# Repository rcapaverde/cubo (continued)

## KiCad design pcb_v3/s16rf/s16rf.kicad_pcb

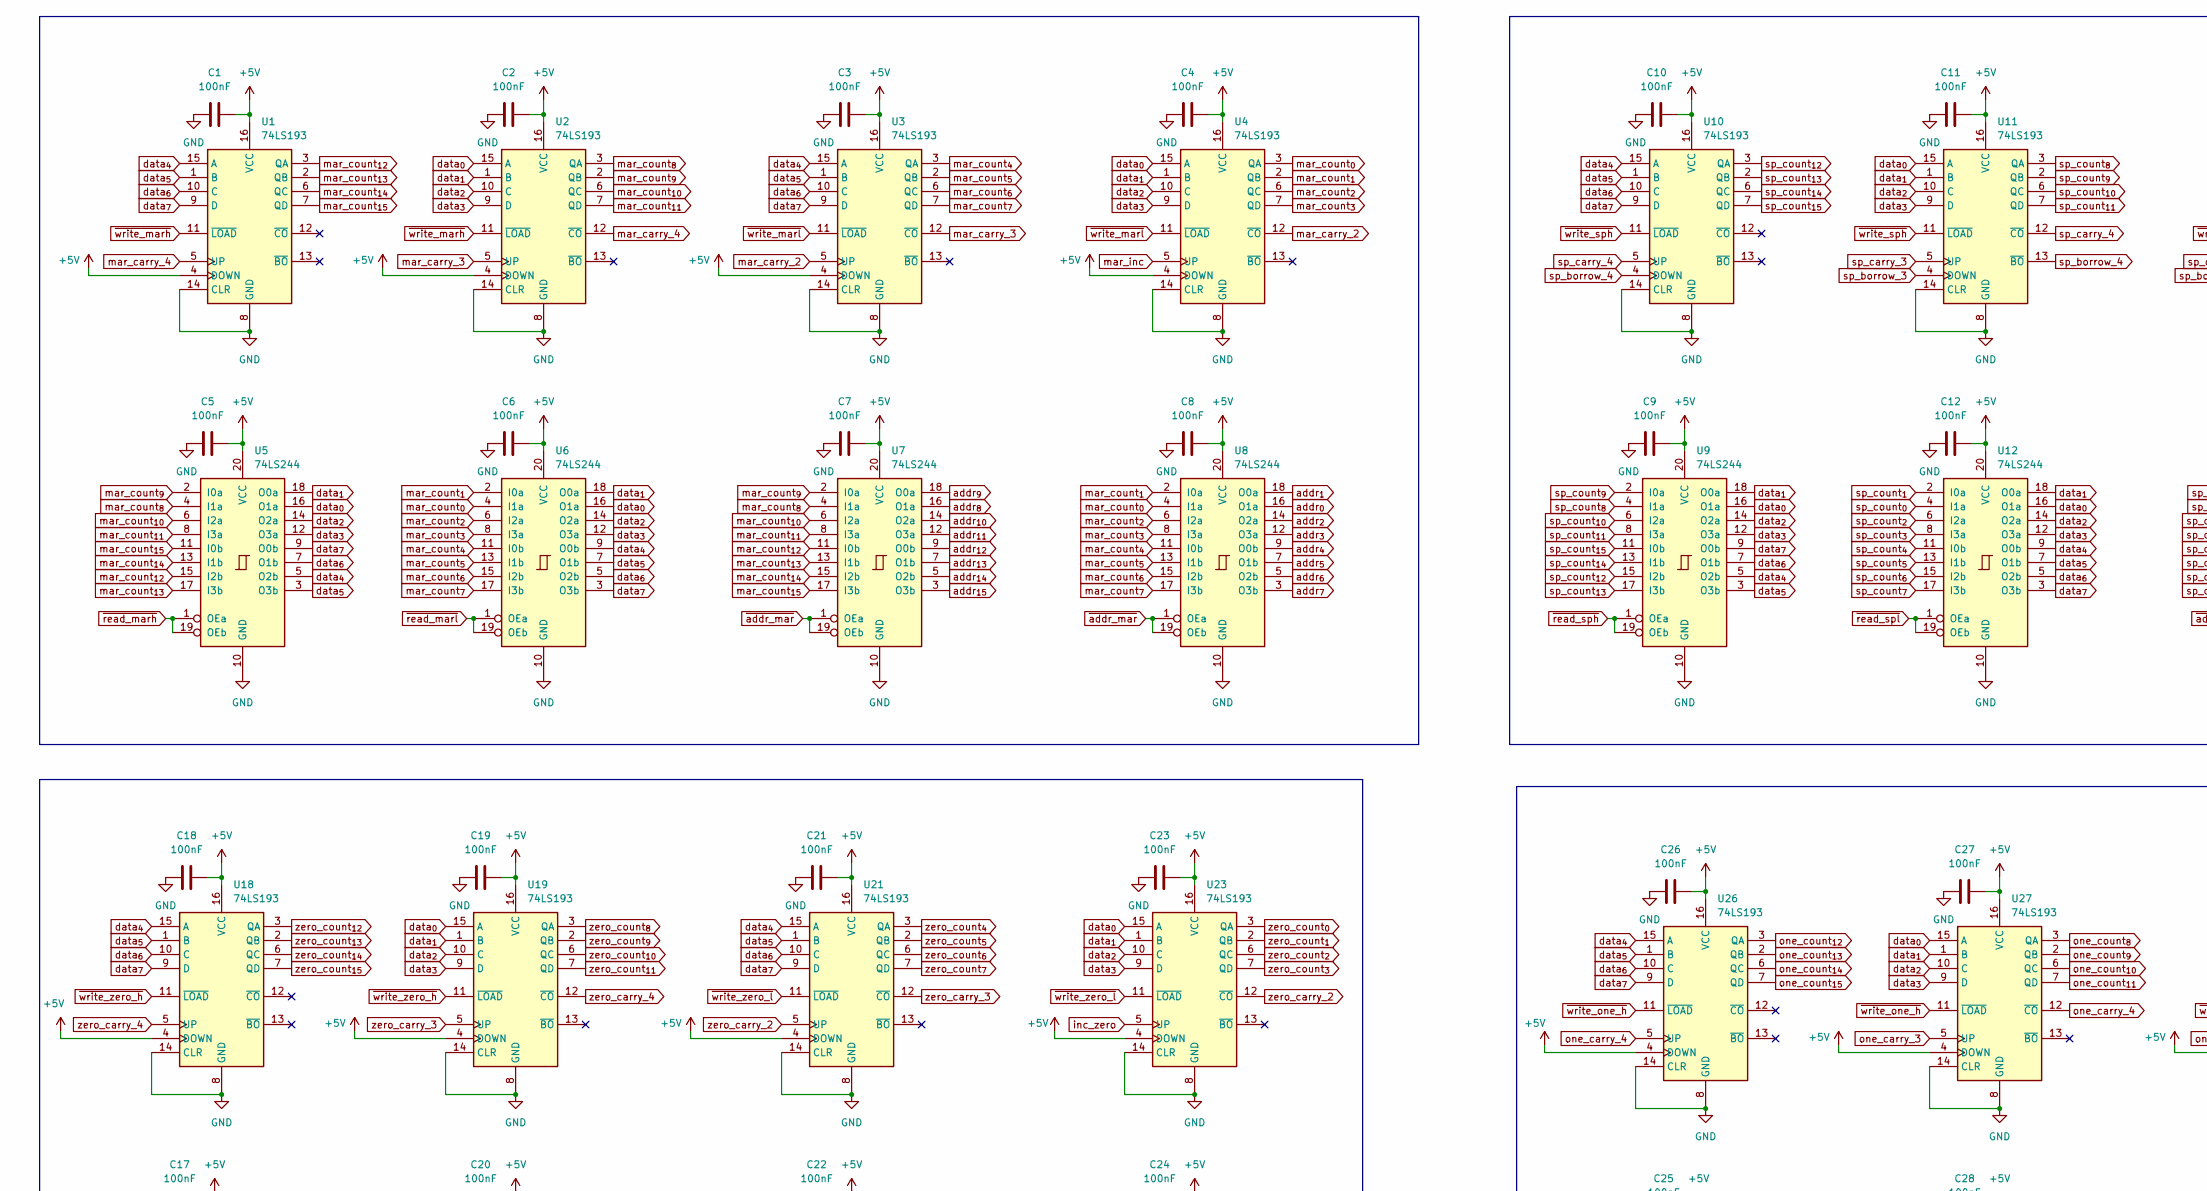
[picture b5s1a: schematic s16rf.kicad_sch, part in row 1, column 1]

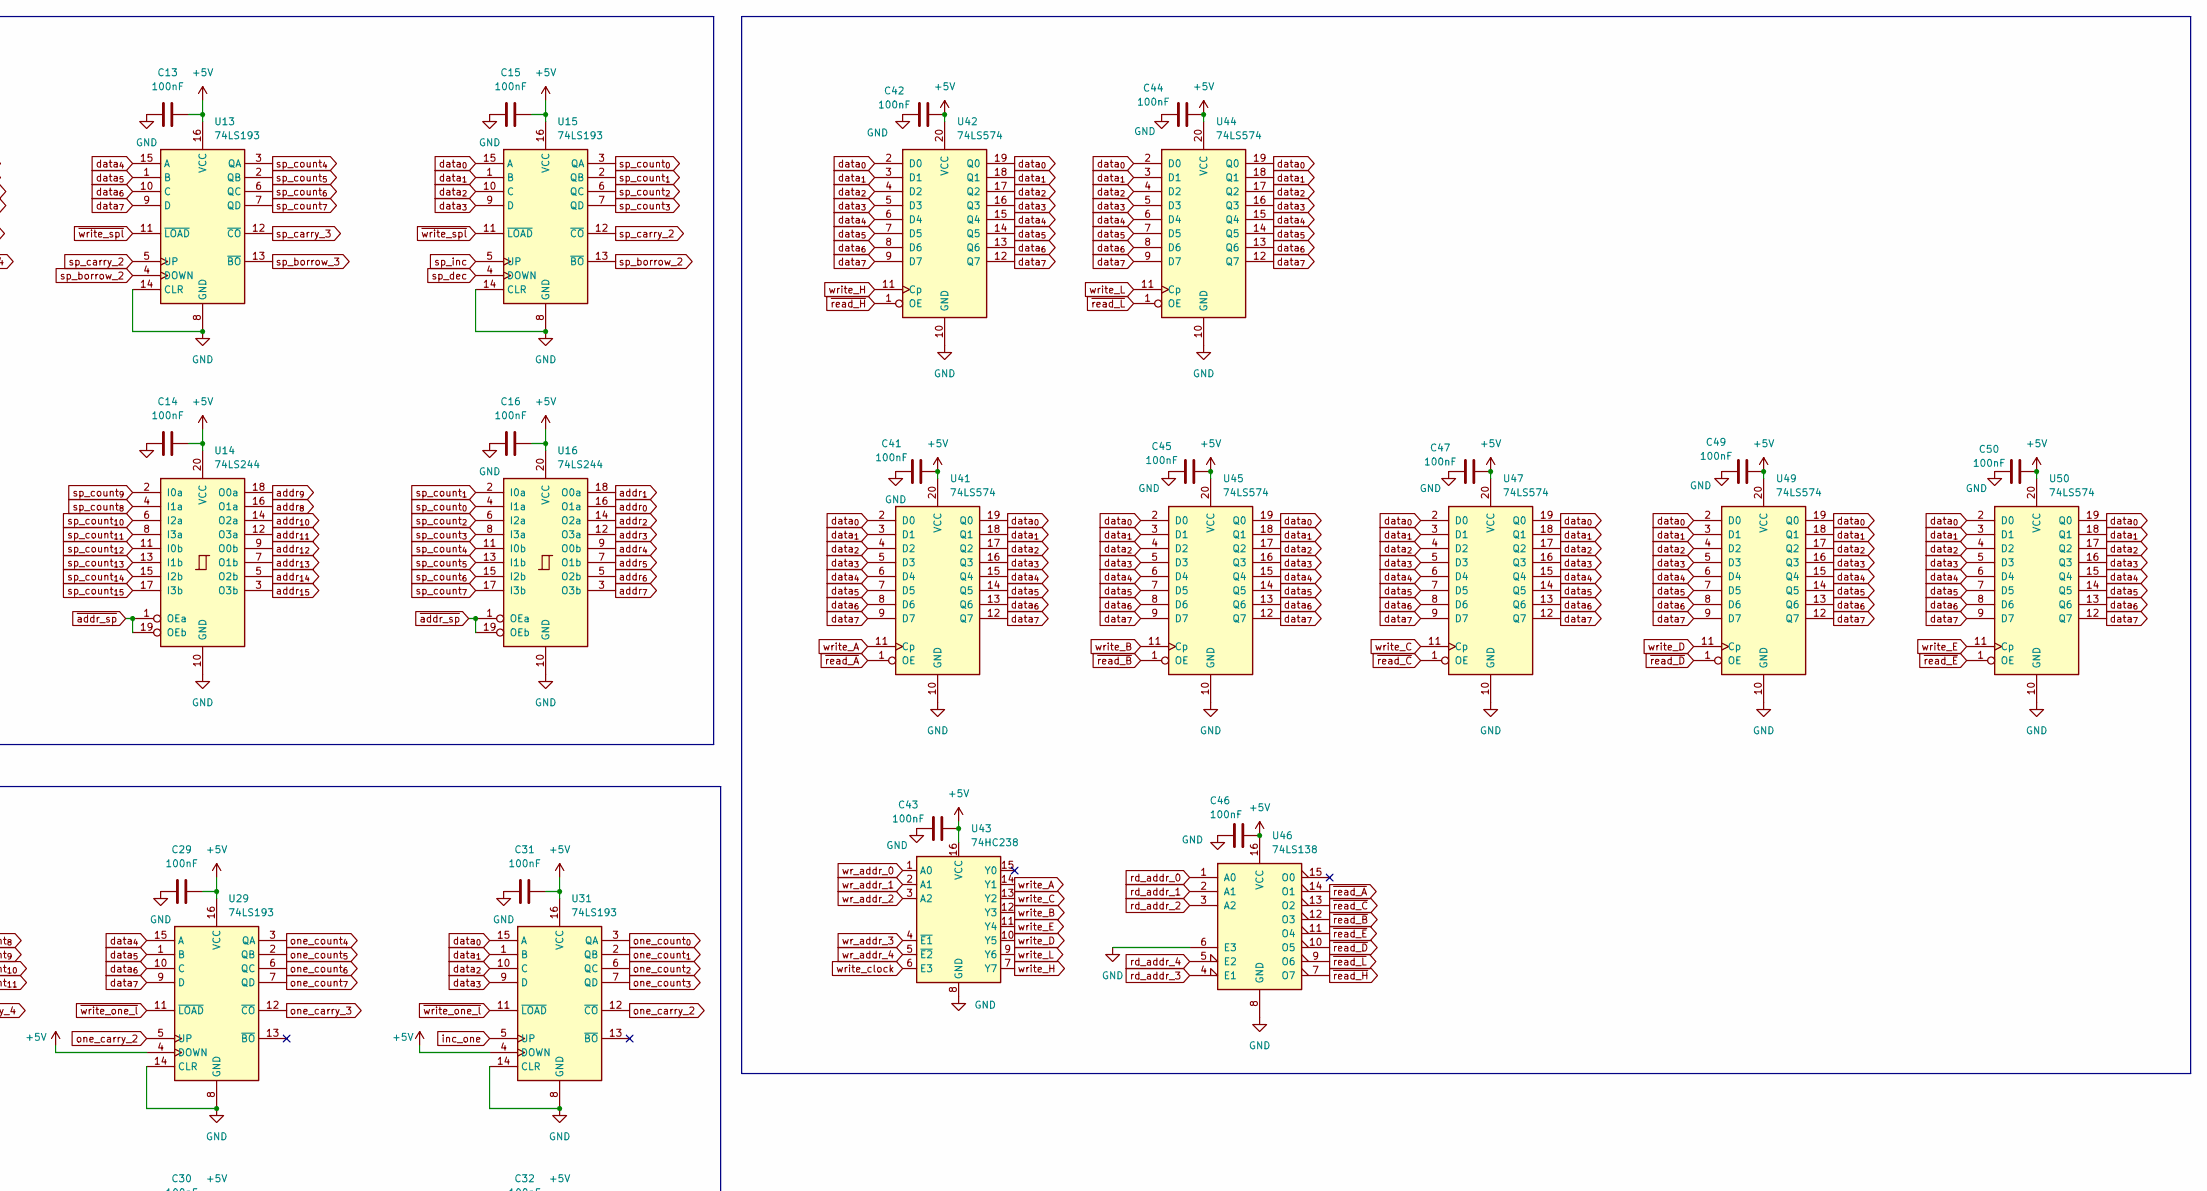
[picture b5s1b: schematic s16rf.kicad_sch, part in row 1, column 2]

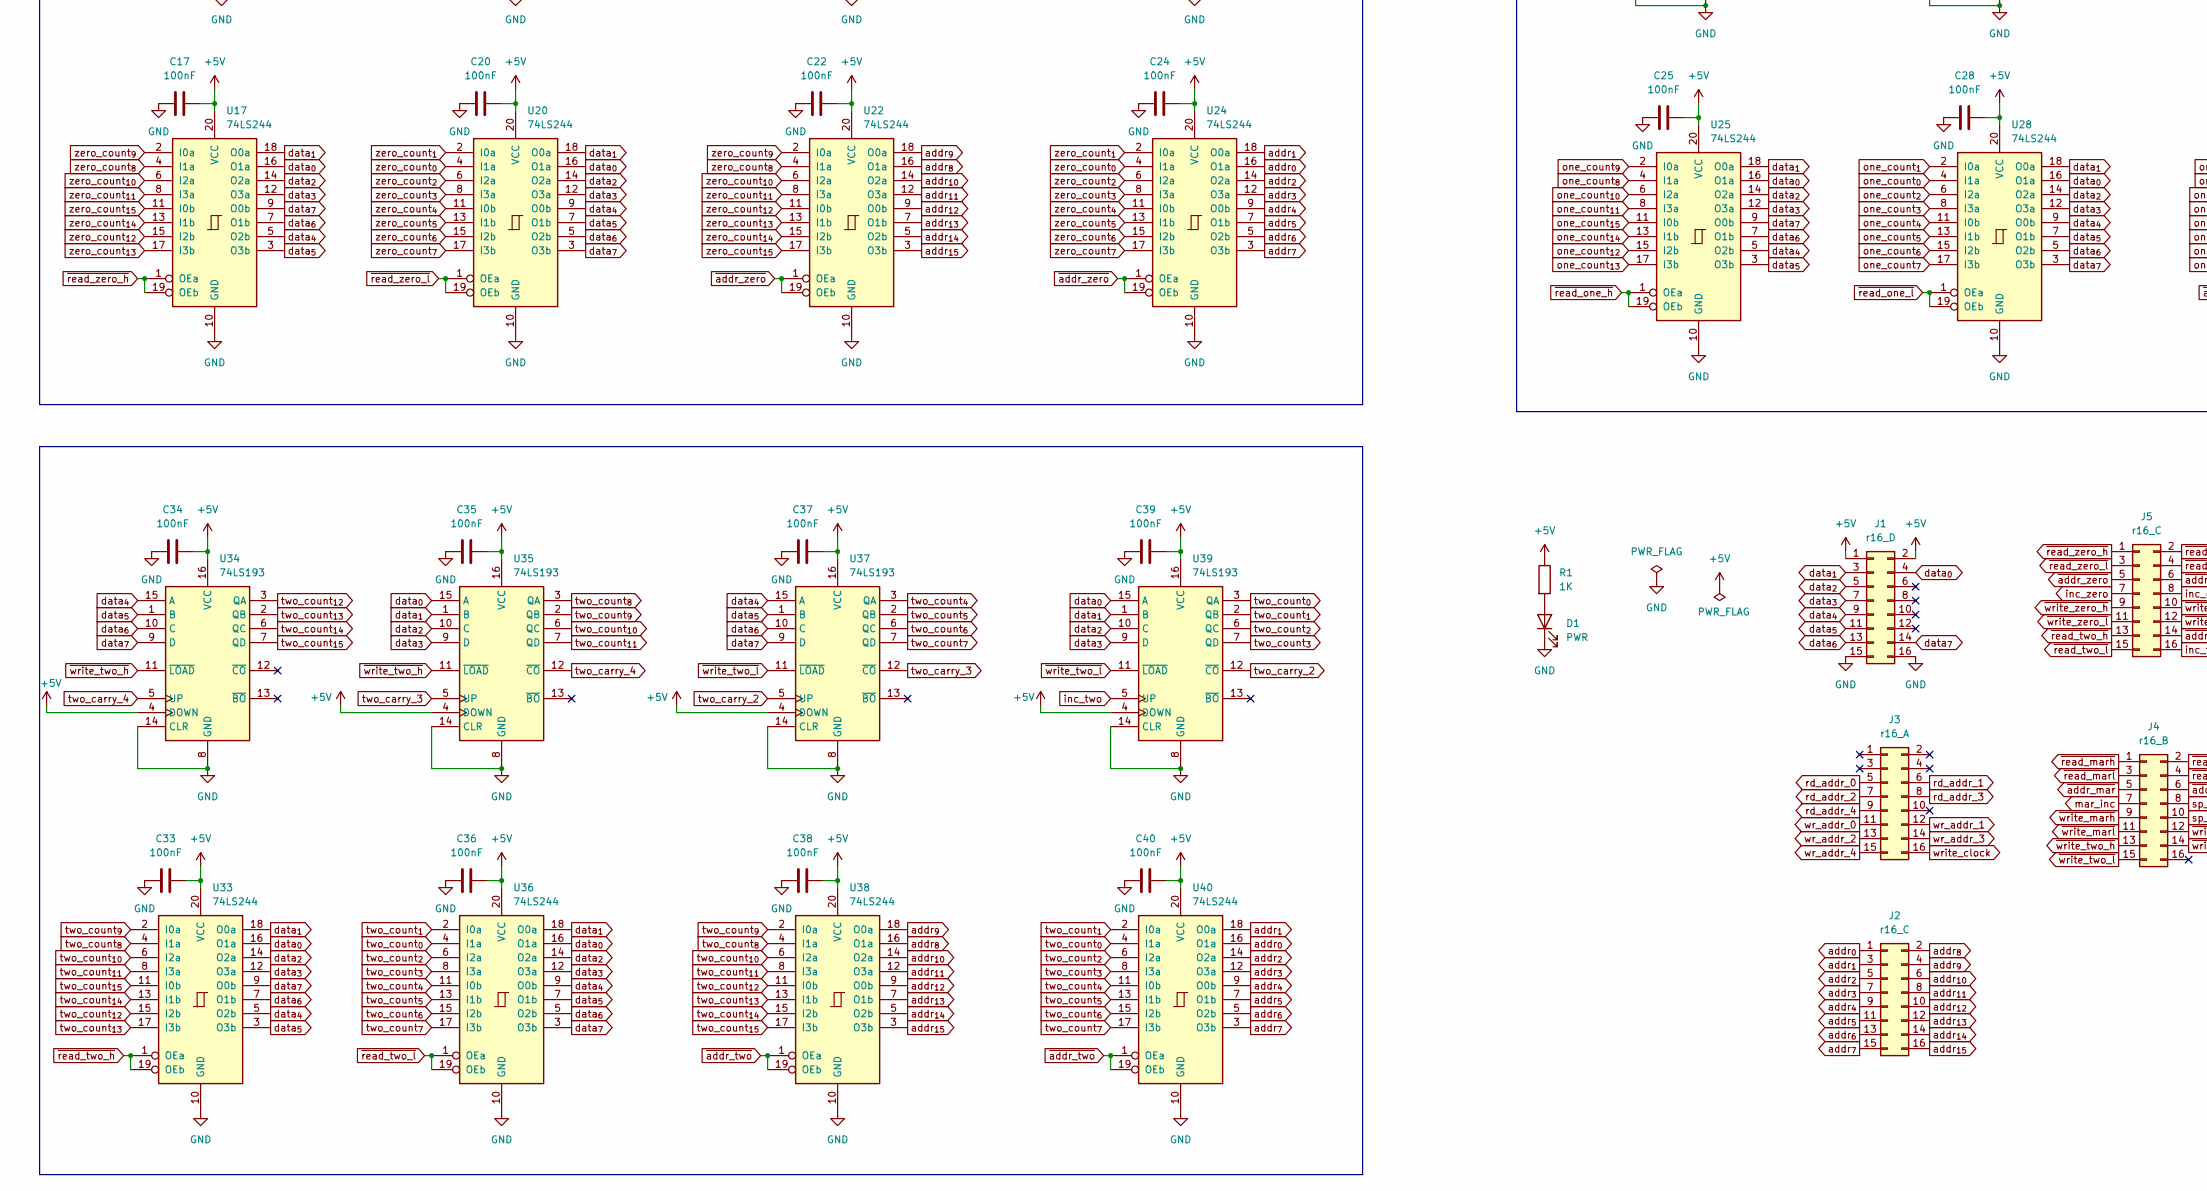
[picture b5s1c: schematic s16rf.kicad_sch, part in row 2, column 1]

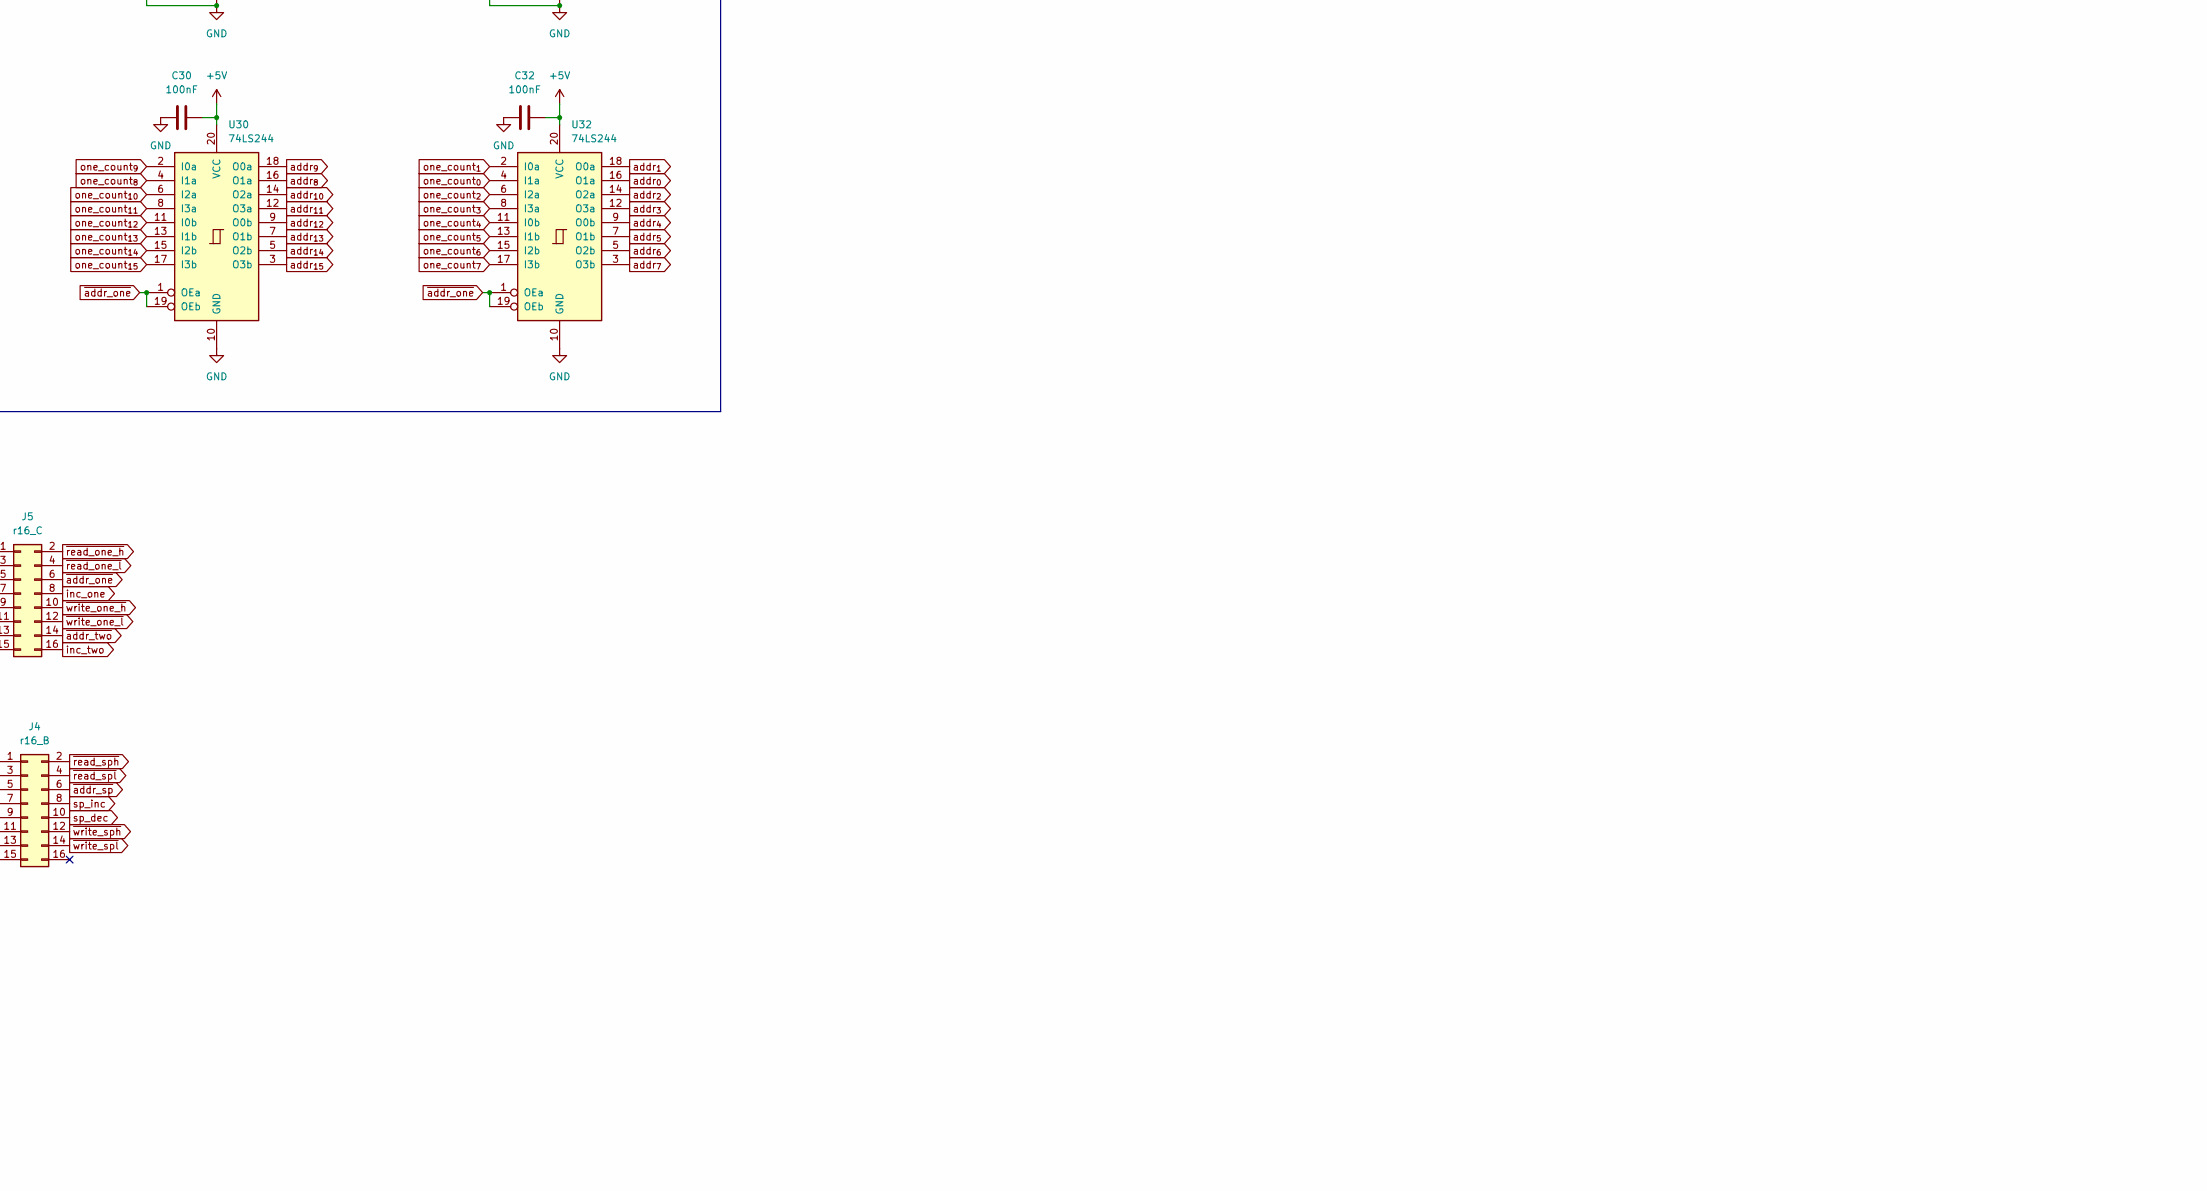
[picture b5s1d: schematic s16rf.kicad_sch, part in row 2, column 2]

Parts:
C1, C2, C3, C4, C5, C6, C7, C8, C9, C10, C11, C12, C13, C14, C15, C16, C17, C18, C19, C20, C21, C22, C23, C24, C25, C26, C27, C28, C29, C30, C31, C32, C33, C34, C35, C36, C37, C38, C39, C40, C41, C42, C43, C44, C45, C46, C47, C49, C50: 100nF; C_Disc_D5.1mm_W3.2mm_P5.00mm
D1: PWR; LED_D5.0mm
J1: r16_D; conector 02x08
J2, J5: r16_C; conector 02x08
J3: r16_A; conector 02x08
J4: r16_B; conector 02x08
R1: 1K; R_Axial_DIN0204_L3.6mm_D1.6mm_P7.62mm_Horizontal
U1, U2, U3, U4, U10, U11, U13, U15, U18, U19, U21, U23, U26, U27, U29, U31, U34, U35, U37, U39: 74LS193; DIP-16_W7.62mm
U5, U6, U7, U8, U9, U12, U14, U16, U17, U20, U22, U24, U25, U28, U30, U32, U33, U36, U38, U40: 74LS244; DIP-20_W7.62mm
U41, U42, U44, U45, U47, U49, U50: 74LS574; DIP-20_W7.62mm
U43: 74HC238; DIP-16_W7.62mm
U46: 74LS138; DIP-16_W7.62mm

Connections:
+5V: C1.2, C2.2, C3.2, C4.2, C5.2, C6.2, C7.2, C8.2, C9.2, C10.2, C11.2, C12.2, C13.2, C14.2, C15.2, C16.2, C17.2, C18.2, C19.2, C20.2, C21.2, C22.2, C23.2, C24.2, C25.2, C26.2, C27.2, C28.2, C29.2, C30.2, C31.2, C32.2, C33.2, C34.2, C35.2, C36.2, C37.2, C38.2, C39.2, C40.2, C41.2, C42.2, C43.2, C44.2, C45.2, C46.2, C47.2, C49.2, C50.2, J1.1, J1.2, R1.1, U1.4 (DOWN), U1.16 (VCC), U2.4 (DOWN), U2.16 (VCC), U3.4 (DOWN), U3.16 (VCC), U4.4 (DOWN), U4.16 (VCC), U5.20 (VCC), U6.20 (VCC), U7.20 (VCC), U8.20 (VCC), U9.20 (VCC), U10.16 (VCC), U11.16 (VCC), U12.20 (VCC), U13.16 (VCC), U14.20 (VCC), U15.16 (VCC), U16.20 (VCC), U17.20 (VCC), U18.4 (DOWN), U18.16 (VCC), U19.4 (DOWN), U19.16 (VCC), U20.20 (VCC), U21.4 (DOWN), U21.16 (VCC), U22.20 (VCC), U23.4 (DOWN), U23.16 (VCC), U24.20 (VCC), U25.20 (VCC), U26.4 (DOWN), U26.16 (VCC), U27.4 (DOWN), U27.16 (VCC), U28.20 (VCC), U29.4 (DOWN), U29.16 (VCC), U30.20 (VCC), U31.4 (DOWN), U31.16 (VCC), U32.20 (VCC), U33.20 (VCC), U34.4 (DOWN), U34.16 (VCC), U35.4 (DOWN), U35.16 (VCC), U36.20 (VCC), U37.4 (DOWN), U37.16 (VCC), U38.20 (VCC), U39.4 (DOWN), U39.16 (VCC), U40.20 (VCC), U41.20 (VCC), U42.20 (VCC), U43.16 (VCC), U44.20 (VCC), U45.20 (VCC), U46.16 (VCC), U47.20 (VCC), U49.20 (VCC), U50.20 (VCC)
GND: C1.1, C2.1, C3.1, C4.1, C5.1, C6.1, C7.1, C8.1, C9.1, C10.1, C11.1, C12.1, C13.1, C14.1, C15.1, C16.1, C17.1, C18.1, C19.1, C20.1, C21.1, C22.1, C23.1, C24.1, C25.1, C26.1, C27.1, C28.1, C29.1, C30.1, C31.1, C32.1, C33.1, C34.1, C35.1, C36.1, C37.1, C38.1, C39.1, C40.1, C41.1, C42.1, C43.1, C44.1, C45.1, C46.1, C47.1, C49.1, C50.1, D1.1 (K), J1.15, J1.16, U1.8 (GND), U1.14 (CLR), U2.8 (GND), U2.14 (CLR), U3.8 (GND), U3.14 (CLR), U4.8 (GND), U4.14 (CLR), U5.10 (GND), U6.10 (GND), U7.10 (GND), U8.10 (GND), U9.10 (GND), U10.8 (GND), U10.14 (CLR), U11.8 (GND), U11.14 (CLR), U12.10 (GND), U13.8 (GND), U13.14 (CLR), U14.10 (GND), U15.8 (GND), U15.14 (CLR), U16.10 (GND), U17.10 (GND), U18.8 (GND), U18.14 (CLR), U19.8 (GND), U19.14 (CLR), U20.10 (GND), U21.8 (GND), U21.14 (CLR), U22.10 (GND), U23.8 (GND), U23.14 (CLR), U24.10 (GND), U25.10 (GND), U26.8 (GND), U26.14 (CLR), U27.8 (GND), U27.14 (CLR), U28.10 (GND), U29.8 (GND), U29.14 (CLR), U30.10 (GND), U31.8 (GND), U31.14 (CLR), U32.10 (GND), U33.10 (GND), U34.8 (GND), U34.14 (CLR), U35.8 (GND), U35.14 (CLR), U36.10 (GND), U37.8 (GND), U37.14 (CLR), U38.10 (GND), U39.8 (GND), U39.14 (CLR), U40.10 (GND), U41.10 (GND), U42.10 (GND), U43.8 (GND), U44.10 (GND), U45.10 (GND), U46.6 (E3), U46.8 (GND), U47.10 (GND), U49.10 (GND), U50.10 (GND)
unnamed: D1.2 (A), R1.2
addr_{0}: J2.1, U8.16 (O1a), U16.16 (O1a), U24.16 (O1a), U32.16 (O1a), U40.16 (O1a)
addr_{1}: J2.3, U8.18 (O0a), U16.18 (O0a), U24.18 (O0a), U32.18 (O0a), U40.18 (O0a)
addr_{2}: J2.5, U8.14 (O2a), U16.14 (O2a), U24.14 (O2a), U32.14 (O2a), U40.14 (O2a)
addr_{3}: J2.7, U8.12 (O3a), U16.12 (O3a), U24.12 (O3a), U32.12 (O3a), U40.12 (O3a)
addr_{4}: J2.9, U8.9 (O0b), U16.9 (O0b), U24.9 (O0b), U32.9 (O0b), U40.9 (O0b)
addr_{5}: J2.11, U8.7 (O1b), U16.7 (O1b), U24.7 (O1b), U32.7 (O1b), U40.7 (O1b)
addr_{6}: J2.13, U8.5 (O2b), U16.5 (O2b), U24.5 (O2b), U32.5 (O2b), U40.5 (O2b)
addr_{7}: J2.15, U8.3 (O3b), U16.3 (O3b), U24.3 (O3b), U32.3 (O3b), U40.3 (O3b)
addr_{8}: J2.2, U7.16 (O1a), U14.16 (O1a), U22.16 (O1a), U30.16 (O1a), U38.16 (O1a)
addr_{9}: J2.4, U7.18 (O0a), U14.18 (O0a), U22.18 (O0a), U30.18 (O0a), U38.18 (O0a)
addr_{10}: J2.6, U7.14 (O2a), U14.14 (O2a), U22.14 (O2a), U30.14 (O2a), U38.14 (O2a)
addr_{11}: J2.8, U7.12 (O3a), U14.12 (O3a), U22.12 (O3a), U30.12 (O3a), U38.12 (O3a)
addr_{12}: J2.10, U7.9 (O0b), U14.9 (O0b), U22.9 (O0b), U30.9 (O0b), U38.9 (O0b)
addr_{13}: J2.12, U7.7 (O1b), U14.7 (O1b), U22.7 (O1b), U30.7 (O1b), U38.7 (O1b)
addr_{14}: J2.14, U7.5 (O2b), U14.5 (O2b), U22.5 (O2b), U30.5 (O2b), U38.5 (O2b)
addr_{15}: J2.16, U7.3 (O3b), U14.3 (O3b), U22.3 (O3b), U30.3 (O3b), U38.3 (O3b)
data_{0}: J1.4, U2.15 (A), U4.15 (A), U5.16 (O1a), U6.16 (O1a), U9.16 (O1a), U11.15 (A), U12.16 (O1a), U15.15 (A), U17.16 (O1a), U19.15 (A), U20.16 (O1a), U23.15 (A), U25.16 (O1a), U27.15 (A), U28.16 (O1a), U31.15 (A), U33.16 (O1a), U35.15 (A), U36.16 (O1a), U39.15 (A), U41.2 (D0), U41.19 (Q0), U42.2 (D0), U42.19 (Q0), U44.2 (D0), U44.19 (Q0), U45.2 (D0), U45.19 (Q0), U47.2 (D0), U47.19 (Q0), U49.2 (D0), U49.19 (Q0), U50.2 (D0), U50.19 (Q0)
data_{1}: J1.3, U2.1 (B), U4.1 (B), U5.18 (O0a), U6.18 (O0a), U9.18 (O0a), U11.1 (B), U12.18 (O0a), U15.1 (B), U17.18 (O0a), U19.1 (B), U20.18 (O0a), U23.1 (B), U25.18 (O0a), U27.1 (B), U28.18 (O0a), U31.1 (B), U33.18 (O0a), U35.1 (B), U36.18 (O0a), U39.1 (B), U41.3 (D1), U41.18 (Q1), U42.3 (D1), U42.18 (Q1), U44.3 (D1), U44.18 (Q1), U45.3 (D1), U45.18 (Q1), U47.3 (D1), U47.18 (Q1), U49.3 (D1), U49.18 (Q1), U50.3 (D1), U50.18 (Q1)
data_{2}: J1.5, U2.10 (C), U4.10 (C), U5.14 (O2a), U6.14 (O2a), U9.14 (O2a), U11.10 (C), U12.14 (O2a), U15.10 (C), U17.14 (O2a), U19.10 (C), U20.14 (O2a), U23.10 (C), U25.14 (O2a), U27.10 (C), U28.14 (O2a), U31.10 (C), U33.14 (O2a), U35.10 (C), U36.14 (O2a), U39.10 (C), U41.4 (D2), U41.17 (Q2), U42.4 (D2), U42.17 (Q2), U44.4 (D2), U44.17 (Q2), U45.4 (D2), U45.17 (Q2), U47.4 (D2), U47.17 (Q2), U49.4 (D2), U49.17 (Q2), U50.4 (D2), U50.17 (Q2)
data_{3}: J1.7, U2.9 (D), U4.9 (D), U5.12 (O3a), U6.12 (O3a), U9.12 (O3a), U11.9 (D), U12.12 (O3a), U15.9 (D), U17.12 (O3a), U19.9 (D), U20.12 (O3a), U23.9 (D), U25.12 (O3a), U27.9 (D), U28.12 (O3a), U31.9 (D), U33.12 (O3a), U35.9 (D), U36.12 (O3a), U39.9 (D), U41.5 (D3), U41.16 (Q3), U42.5 (D3), U42.16 (Q3), U44.5 (D3), U44.16 (Q3), U45.5 (D3), U45.16 (Q3), U47.5 (D3), U47.16 (Q3), U49.5 (D3), U49.16 (Q3), U50.5 (D3), U50.16 (Q3)
data_{4}: J1.9, U1.15 (A), U3.15 (A), U5.5 (O2b), U6.9 (O0b), U9.5 (O2b), U10.15 (A), U12.9 (O0b), U13.15 (A), U17.5 (O2b), U18.15 (A), U20.9 (O0b), U21.15 (A), U25.5 (O2b), U26.15 (A), U28.9 (O0b), U29.15 (A), U33.5 (O2b), U34.15 (A), U36.9 (O0b), U37.15 (A), U41.6 (D4), U41.15 (Q4), U42.6 (D4), U42.15 (Q4), U44.6 (D4), U44.15 (Q4), U45.6 (D4), U45.15 (Q4), U47.6 (D4), U47.15 (Q4), U49.6 (D4), U49.15 (Q4), U50.6 (D4), U50.15 (Q4)
data_{5}: J1.11, U1.1 (B), U3.1 (B), U5.3 (O3b), U6.7 (O1b), U9.3 (O3b), U10.1 (B), U12.7 (O1b), U13.1 (B), U17.3 (O3b), U18.1 (B), U20.7 (O1b), U21.1 (B), U25.3 (O3b), U26.1 (B), U28.7 (O1b), U29.1 (B), U33.3 (O3b), U34.1 (B), U36.7 (O1b), U37.1 (B), U41.7 (D5), U41.14 (Q5), U42.7 (D5), U42.14 (Q5), U44.7 (D5), U44.14 (Q5), U45.7 (D5), U45.14 (Q5), U47.7 (D5), U47.14 (Q5), U49.7 (D5), U49.14 (Q5), U50.7 (D5), U50.14 (Q5)
data_{6}: J1.13, U1.10 (C), U3.10 (C), U5.7 (O1b), U6.5 (O2b), U9.7 (O1b), U10.10 (C), U12.5 (O2b), U13.10 (C), U17.7 (O1b), U18.10 (C), U20.5 (O2b), U21.10 (C), U25.7 (O1b), U26.10 (C), U28.5 (O2b), U29.10 (C), U33.7 (O1b), U34.10 (C), U36.5 (O2b), U37.10 (C), U41.8 (D6), U41.13 (Q6), U42.8 (D6), U42.13 (Q6), U44.8 (D6), U44.13 (Q6), U45.8 (D6), U45.13 (Q6), U47.8 (D6), U47.13 (Q6), U49.8 (D6), U49.13 (Q6), U50.8 (D6), U50.13 (Q6)
data_{7}: J1.14, U1.9 (D), U3.9 (D), U5.9 (O0b), U6.3 (O3b), U9.9 (O0b), U10.9 (D), U12.3 (O3b), U13.9 (D), U17.9 (O0b), U18.9 (D), U20.3 (O3b), U21.9 (D), U25.9 (O0b), U26.9 (D), U28.3 (O3b), U29.9 (D), U33.9 (O0b), U34.9 (D), U36.3 (O3b), U37.9 (D), U41.9 (D7), U41.12 (Q7), U42.9 (D7), U42.12 (Q7), U44.9 (D7), U44.12 (Q7), U45.9 (D7), U45.12 (Q7), U47.9 (D7), U47.12 (Q7), U49.9 (D7), U49.12 (Q7), U50.9 (D7), U50.12 (Q7)
inc_one: J5.8, U31.5 (UP)
inc_two: J5.16, U39.5 (UP)
inc_zero: J5.7, U23.5 (UP)
mar_carry_2: U3.5 (UP), U4.12 (~CO)
mar_carry_3: U2.5 (UP), U3.12 (~CO)
mar_carry_4: U1.5 (UP), U2.12 (~CO)
mar_count_{0}: U4.3 (QA), U6.4 (I1a), U8.4 (I1a)
mar_count_{1}: U4.2 (QB), U6.2 (I0a), U8.2 (I0a)
mar_count_{2}: U4.6 (QC), U6.6 (I2a), U8.6 (I2a)
mar_count_{3}: U4.7 (QD), U6.8 (I3a), U8.8 (I3a)
mar_count_{4}: U3.3 (QA), U6.11 (I0b), U8.11 (I0b)
mar_count_{5}: U3.2 (QB), U6.13 (I1b), U8.13 (I1b)
mar_count_{6}: U3.6 (QC), U6.15 (I2b), U8.15 (I2b)
mar_count_{7}: U3.7 (QD), U6.17 (I3b), U8.17 (I3b)
mar_count_{8}: U2.3 (QA), U5.4 (I1a), U7.4 (I1a)
mar_count_{9}: U2.2 (QB), U5.2 (I0a), U7.2 (I0a)
mar_count_{10}: U2.6 (QC), U5.6 (I2a), U7.6 (I2a)
mar_count_{11}: U2.7 (QD), U5.8 (I3a), U7.8 (I3a)
mar_count_{12}: U1.3 (QA), U5.15 (I2b), U7.11 (I0b)
mar_count_{13}: U1.2 (QB), U5.17 (I3b), U7.13 (I1b)
mar_count_{14}: U1.6 (QC), U5.13 (I1b), U7.15 (I2b)
mar_count_{15}: U1.7 (QD), U5.11 (I0b), U7.17 (I3b)
mar_inc: J4.7, U4.5 (UP)
one_carry_2: U29.5 (UP), U31.12 (~CO)
one_carry_3: U27.5 (UP), U29.12 (~CO)
one_carry_4: U26.5 (UP), U27.12 (~CO)
one_count_{0}: U28.4 (I1a), U31.3 (QA), U32.4 (I1a)
one_count_{1}: U28.2 (I0a), U31.2 (QB), U32.2 (I0a)
one_count_{2}: U28.6 (I2a), U31.6 (QC), U32.6 (I2a)
one_count_{3}: U28.8 (I3a), U31.7 (QD), U32.8 (I3a)
one_count_{4}: U28.11 (I0b), U29.3 (QA), U32.11 (I0b)
one_count_{5}: U28.13 (I1b), U29.2 (QB), U32.13 (I1b)
one_count_{6}: U28.15 (I2b), U29.6 (QC), U32.15 (I2b)
one_count_{7}: U28.17 (I3b), U29.7 (QD), U32.17 (I3b)
one_count_{8}: U25.4 (I1a), U27.3 (QA), U30.4 (I1a)
one_count_{9}: U25.2 (I0a), U27.2 (QB), U30.2 (I0a)
one_count_{10}: U25.6 (I2a), U27.6 (QC), U30.6 (I2a)
one_count_{11}: U25.8 (I3a), U27.7 (QD), U30.8 (I3a)
one_count_{12}: U25.15 (I2b), U26.3 (QA), U30.11 (I0b)
one_count_{13}: U25.17 (I3b), U26.2 (QB), U30.13 (I1b)
one_count_{14}: U25.13 (I1b), U26.6 (QC), U30.15 (I2b)
one_count_{15}: U25.11 (I0b), U26.7 (QD), U30.17 (I3b)
rd_addr_0: J3.5, U46.1 (A0)
rd_addr_1: J3.6, U46.2 (A1)
rd_addr_2: J3.7, U46.3 (A2)
rd_addr_3: J3.8, U46.4 (E1)
rd_addr_4: J3.9, U46.5 (E2)
sp_borrow_2: U13.4 (DOWN), U15.13 (~BO)
sp_borrow_3: U11.4 (DOWN), U13.13 (~BO)
sp_borrow_4: U10.4 (DOWN), U11.13 (~BO)
sp_carry_2: U13.5 (UP), U15.12 (~CO)
sp_carry_3: U11.5 (UP), U13.12 (~CO)
sp_carry_4: U10.5 (UP), U11.12 (~CO)
sp_count_{0}: U12.4 (I1a), U15.3 (QA), U16.4 (I1a)
sp_count_{1}: U12.2 (I0a), U15.2 (QB), U16.2 (I0a)
sp_count_{2}: U12.6 (I2a), U15.6 (QC), U16.6 (I2a)
sp_count_{3}: U12.8 (I3a), U15.7 (QD), U16.8 (I3a)
sp_count_{4}: U12.11 (I0b), U13.3 (QA), U16.11 (I0b)
sp_count_{5}: U12.13 (I1b), U13.2 (QB), U16.13 (I1b)
sp_count_{6}: U12.15 (I2b), U13.6 (QC), U16.15 (I2b)
sp_count_{7}: U12.17 (I3b), U13.7 (QD), U16.17 (I3b)
sp_count_{8}: U9.4 (I1a), U11.3 (QA), U14.4 (I1a)
sp_count_{9}: U9.2 (I0a), U11.2 (QB), U14.2 (I0a)
sp_count_{10}: U9.6 (I2a), U11.6 (QC), U14.6 (I2a)
sp_count_{11}: U9.8 (I3a), U11.7 (QD), U14.8 (I3a)
sp_count_{12}: U9.15 (I2b), U10.3 (QA), U14.11 (I0b)
sp_count_{13}: U9.17 (I3b), U10.2 (QB), U14.13 (I1b)
sp_count_{14}: U9.13 (I1b), U10.6 (QC), U14.15 (I2b)
sp_count_{15}: U9.11 (I0b), U10.7 (QD), U14.17 (I3b)
sp_dec: J4.10, U15.4 (DOWN)
sp_inc: J4.8, U15.5 (UP)
two_carry_2: U37.5 (UP), U39.12 (~CO)
two_carry_3: U35.5 (UP), U37.12 (~CO)
two_carry_4: U34.5 (UP), U35.12 (~CO)
two_count_{0}: U36.4 (I1a), U39.3 (QA), U40.4 (I1a)
two_count_{1}: U36.2 (I0a), U39.2 (QB), U40.2 (I0a)
two_count_{2}: U36.6 (I2a), U39.6 (QC), U40.6 (I2a)
two_count_{3}: U36.8 (I3a), U39.7 (QD), U40.8 (I3a)
two_count_{4}: U36.11 (I0b), U37.3 (QA), U40.11 (I0b)
two_count_{5}: U36.13 (I1b), U37.2 (QB), U40.13 (I1b)
two_count_{6}: U36.15 (I2b), U37.6 (QC), U40.15 (I2b)
two_count_{7}: U36.17 (I3b), U37.7 (QD), U40.17 (I3b)
two_count_{8}: U33.4 (I1a), U35.3 (QA), U38.4 (I1a)
two_count_{9}: U33.2 (I0a), U35.2 (QB), U38.2 (I0a)
two_count_{10}: U33.6 (I2a), U35.6 (QC), U38.6 (I2a)
two_count_{11}: U33.8 (I3a), U35.7 (QD), U38.8 (I3a)
two_count_{12}: U33.15 (I2b), U34.3 (QA), U38.11 (I0b)
two_count_{13}: U33.17 (I3b), U34.2 (QB), U38.13 (I1b)
two_count_{14}: U33.13 (I1b), U34.6 (QC), U38.15 (I2b)
two_count_{15}: U33.11 (I0b), U34.7 (QD), U38.17 (I3b)
wr_addr_0: J3.11, U43.1 (A0)
wr_addr_1: J3.12, U43.2 (A1)
wr_addr_2: J3.13, U43.3 (A2)
wr_addr_3: J3.14, U43.4 (~E1)
wr_addr_4: J3.15, U43.5 (~E2)
write_A: U41.11 (Cp), U43.14 (Y1)
write_B: U43.12 (Y3), U45.11 (Cp)
write_C: U43.13 (Y2), U47.11 (Cp)
write_D: U43.10 (Y5), U49.11 (Cp)
write_E: U43.11 (Y4), U50.11 (Cp)
write_H: U42.11 (Cp), U43.7 (Y7)
write_L: U43.9 (Y6), U44.11 (Cp)
write_clock: J3.16, U43.6 (E3)
zero_carry_2: U21.5 (UP), U23.12 (~CO)
zero_carry_3: U19.5 (UP), U21.12 (~CO)
zero_carry_4: U18.5 (UP), U19.12 (~CO)
zero_count_{0}: U20.4 (I1a), U23.3 (QA), U24.4 (I1a)
zero_count_{1}: U20.2 (I0a), U23.2 (QB), U24.2 (I0a)
zero_count_{2}: U20.6 (I2a), U23.6 (QC), U24.6 (I2a)
zero_count_{3}: U20.8 (I3a), U23.7 (QD), U24.8 (I3a)
zero_count_{4}: U20.11 (I0b), U21.3 (QA), U24.11 (I0b)
zero_count_{5}: U20.13 (I1b), U21.2 (QB), U24.13 (I1b)
zero_count_{6}: U20.15 (I2b), U21.6 (QC), U24.15 (I2b)
zero_count_{7}: U20.17 (I3b), U21.7 (QD), U24.17 (I3b)
zero_count_{8}: U17.4 (I1a), U19.3 (QA), U22.4 (I1a)
zero_count_{9}: U17.2 (I0a), U19.2 (QB), U22.2 (I0a)
zero_count_{10}: U17.6 (I2a), U19.6 (QC), U22.6 (I2a)
zero_count_{11}: U17.8 (I3a), U19.7 (QD), U22.8 (I3a)
zero_count_{12}: U17.15 (I2b), U18.3 (QA), U22.11 (I0b)
zero_count_{13}: U17.17 (I3b), U18.2 (QB), U22.13 (I1b)
zero_count_{14}: U17.13 (I1b), U18.6 (QC), U22.15 (I2b)
zero_count_{15}: U17.11 (I0b), U18.7 (QD), U22.17 (I3b)
~addr_mar: J4.5, U7.1 (OEa), U7.19 (OEb), U8.1 (OEa), U8.19 (OEb)
~addr_one: J5.6, U30.1 (OEa), U30.19 (OEb), U32.1 (OEa), U32.19 (OEb)
~addr_sp: J4.6, U14.1 (OEa), U14.19 (OEb), U16.1 (OEa), U16.19 (OEb)
~addr_two: J5.14, U38.1 (OEa), U38.19 (OEb), U40.1 (OEa), U40.19 (OEb)
~addr_zero: J5.5, U22.1 (OEa), U22.19 (OEb), U24.1 (OEa), U24.19 (OEb)
~read_A: U41.1 (OE), U46.14 (O1)
~read_B: U45.1 (OE), U46.12 (O3)
~read_C: U46.13 (O2), U47.1 (OE)
~read_D: U46.10 (O5), U49.1 (OE)
~read_E: U46.11 (O4), U50.1 (OE)
~read_H: U42.1 (OE), U46.7 (O7)
~read_L: U44.1 (OE), U46.9 (O6)
~read_marh: J4.1, U5.1 (OEa), U5.19 (OEb)
~read_marl: J4.3, U6.1 (OEa), U6.19 (OEb)
~read_one_h: J5.2, U25.1 (OEa), U25.19 (OEb)
~read_one_l: J5.4, U28.1 (OEa), U28.19 (OEb)
~read_sph: J4.2, U9.1 (OEa), U9.19 (OEb)
~read_spl: J4.4, U12.1 (OEa), U12.19 (OEb)
~read_two_h: J5.13, U33.1 (OEa), U33.19 (OEb)
~read_two_l: J5.15, U36.1 (OEa), U36.19 (OEb)
~read_zero_h: J5.1, U17.1 (OEa), U17.19 (OEb)
~read_zero_l: J5.3, U20.1 (OEa), U20.19 (OEb)
~write_marh: J4.9, U1.11 (~LOAD), U2.11 (~LOAD)
~write_marl: J4.11, U3.11 (~LOAD), U4.11 (~LOAD)
~write_one_h: J5.10, U26.11 (~LOAD), U27.11 (~LOAD)
~write_one_l: J5.12, U29.11 (~LOAD), U31.11 (~LOAD)
~write_sph: J4.12, U10.11 (~LOAD), U11.11 (~LOAD)
~write_spl: J4.14, U13.11 (~LOAD), U15.11 (~LOAD)
~write_two_h: J4.13, U34.11 (~LOAD), U35.11 (~LOAD)
~write_two_l: J4.15, U37.11 (~LOAD), U39.11 (~LOAD)
~write_zero_h: J5.9, U18.11 (~LOAD), U19.11 (~LOAD)
~write_zero_l: J5.11, U21.11 (~LOAD), U23.11 (~LOAD)

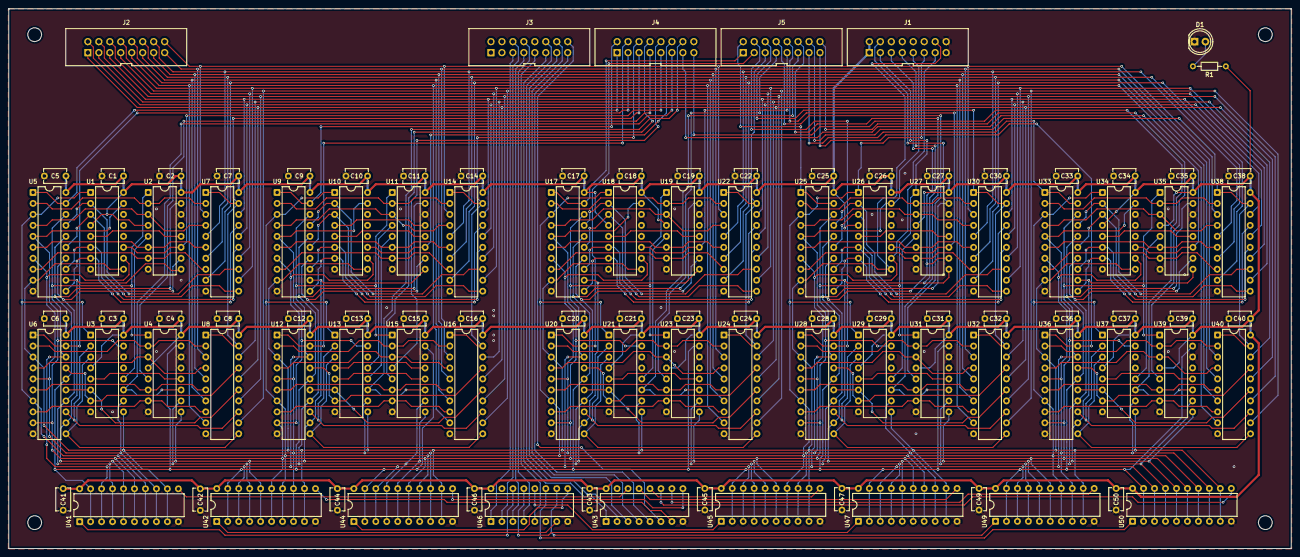
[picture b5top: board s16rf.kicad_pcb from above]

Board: 2 copper layers, 297.0 x 125.0 mm, 105 parts (0 on the bottom side), 181 nets.
